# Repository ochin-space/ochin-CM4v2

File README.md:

# ochin_CM4 v2.0.1
The öchìn CM4 it’s a tiny carrier board for the Raspberry Pi Compute Module  It is designed for applications where a powerful machine with low consumption and small dimensions is required. The small form factor makes it interesting for all those applications where the space available is not much and containing the weight is important, such as in robotics, home automation and IOT.

The board is compatible with all Raspberry Pi CM4 modules equipped with eMMC. Depending on your needs, you can select a CM4 module with an SDRAM starting from 1GB up to 8GB and the eMMC from 8GB up to 32GB, with or without the Wi-Fi/BT module.

Key features of the Raspberry Pi CM4 available on öchìn are as follows:
* Broadcom BCM2711, Quad core Cortex-A72 (ARM v8) 64-bit SoC @ 1.5GHz
* Small Footprint 55mm × 40mm × 4.7mm module
* H.265 (HEVC) (up to 4Kp60 decode), H.264 (up to 1080p60 decode, 1080p30 encode)
* OpenGL ES 3.0 graphics
* Options for 1GB, 2GB, 4GB or 8GB LPDDR4-3200 SDRAM with ECC
* Options for 8GB, 16GB, or 32GB eMMC Flash
o Peak eMMC bandwidth 100MBytes/s
o 2.4 GHz, 5.0 GHz IEEE 802.11 b/g/n/ac wireless
o Bluetooth 5.0, BLE
o On board electronic switch to select between PCB trace or external antenna
* 1×USB 2.0 port (highspeed)

The öchìn CM4v2 board provides the following interfaces:

*	4x USB 2.0 480Mbps (4x SM04B-GHS-TB(LF)(SN) connectors)
*	1x USB Type-C (for flashing eMMC)
*	2x CSI camera (2x FH12-22S-0.5SH (55) connectors)
*	I2C1 (SM04B-GHS-TB(LF)(SN) connector)
*	SPI1 / 6 (SM06B-GHS-TB(LF)(SN) connector)
*	UART0 / 1 + Video Out (SM06B-GHS-TB(LF)(SN) connector)
*	UART4 / UART5 (SM06B-GHS-TB(LF)(SN) connector)
*	1x Ethernet transformerless 100Base-T
*	1x microHDMI
*	2x general purpose LEDs
*	1x RGB LED on external tiny board
*	1x general purpose button on external tiny board

The ochin_CM4v2 card introduces several new features compared to v1, some of which expand the board's capabilities and make it suitable for a wider range of embedded applications. 

Below is a table in which it is possible to see which are the new fetures and which has been removed.

In this repository you can find the [manual](öchìnCM4v2-Manual.pdf) of the board, a quick start guide for flashing the CM4 module and a guide with some tips on how to make the connections to the ochin board. 

It is important to read them both before turning on the ochin_CM4v2 board, to know its characteristics and above all the sequence in which the signals are present on the connectors.

# Intended Use

The öchìn CM4v2 is a general-purpose carrier board intended for civilian applications such as embedded computing, robotics, IoT, home automation, multimedia, computer vision, research and education.

The board is not designed, marketed or intended for military or weapons-related applications. Users are responsible for ensuring that their use of the hardware and software complies with all applicable laws, regulations and export-control requirements.

# Where to buy the ochin_CM4 boards
The ochin_CM4 boards are manufactured and sold by Seeedstudio. You can purchase ochin_CM4 boards from Seeedstudio's marketplace, https://www.seeedstudio.com or from Seeedstudio's business partners (Digikey, Mouser, RS components and many others).

# License Notice for This GitHub Repository

This GitHub repository contains various resources that are subject to specific licenses. Please note the following information regarding the applicable licenses:

* Documentation, Manuals, PDF Schematics, scripts and Other Textual Content: All textual documents present in this repository, including manuals, schematics, and documentation, are released under the GNU Free Documentation License (GFDL).

* Hardware (KiCad Sources, Gerber Files, Assembly Files, etc.): The hardware-related items, including but not limited to KiCad sources, Gerber files, and assembly files, are subject to a proprietary license. This means that these resources are not released as open source and their use is governed by the terms specified in the accompanying documentation or separate terms of use provided.

Please respect the conditions of both licenses when using and distributing the materials in this repository.

For any questions or clarifications regarding the [LICENSE](LICENSE), feel free to contact us.

# Important!!!

Print and use the extractor for the CM4 module if you don't want to break the mezzanines, you can find the [ochin_mount-extractor.stl](3d/CoversTurretsAndExtractors/ochin_mount-extractor.stl) in the "3d/CoversTurretsAndExtractors" section of this repository.

Take a look at the [öchìnCM4v2-WiringAndSuggestions.pdf](öchìnCM4v2-WiringAndSuggestions.pdf) before power the board on, it may save your time and your devices.

Never trust the color code of the GHS cables, the sequence in which commercial GHS cables are assembled is often random and does not reflect the sequence of the signals present in the connectors of the ochin_CM4 board.

Please refer to the file [öchìnCM4v2-HW-bugs.pdf](öchìnCM4v2-HW-bugs.pdf) for details regarding known issues on the board and the respective version in which they were resolved

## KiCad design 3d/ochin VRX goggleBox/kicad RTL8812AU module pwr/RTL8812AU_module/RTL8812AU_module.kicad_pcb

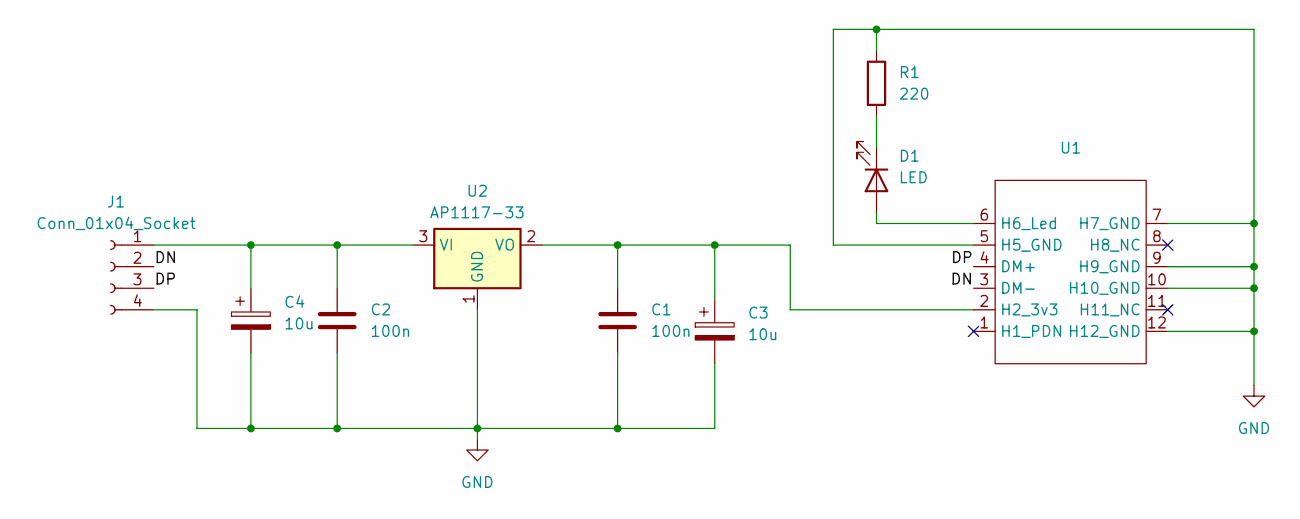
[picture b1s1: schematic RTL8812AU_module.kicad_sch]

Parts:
C1, C2: 100n; C_0805_2012Metric_Pad1.18x1.45mm_HandSolder
C3, C4: 10u; CP_EIA-3216-10_Kemet-I_Pad1.58x1.35mm_HandSolder
D1: LED; LED_0805_2012Metric_Pad1.15x1.40mm_HandSolder
J1: Conn_01x04_Socket; PinHeader_1x04_P2.54mm_Vertical
R1: 220; R_0805_2012Metric_Pad1.20x1.40mm_HandSolder
U1: RTL8812AU
U2: AP1117-33; SOT-223-3_TabPin2

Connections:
/DN: J1.2, U1.3 (DM-)
/DP: J1.3, U1.4 (DM+)
GND: C1.2, C2.2, C3.2, C4.2, J1.4, R1.1, U1.5 (H5_GND), U1.7 (H7_GND), U1.9 (H9_GND), U1.10 (H10_GND), U1.12 (H12_GND), U2.1 (GND)
unnamed: D1.2 (A), U1.6 (H6_Led)
unnamed: D1.1 (K), R1.2
unnamed: C2.1, C4.1, J1.1, U2.3 (VI)
unnamed: C1.1, C3.1, U1.2 (H2_3v3), U2.2 (VO)

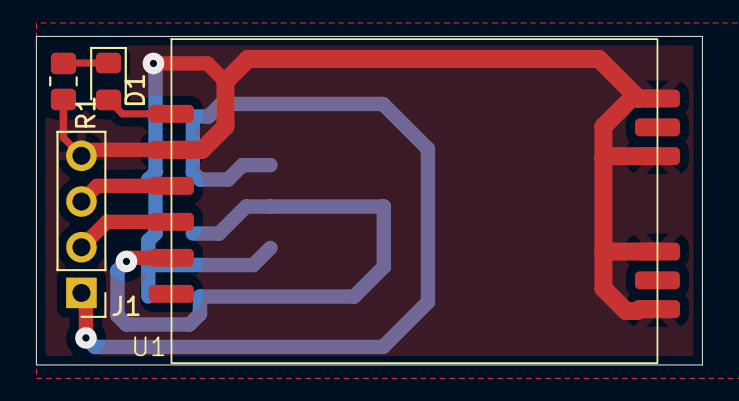
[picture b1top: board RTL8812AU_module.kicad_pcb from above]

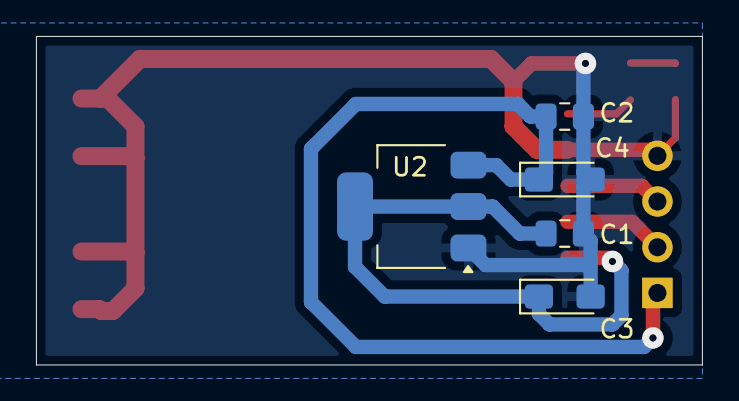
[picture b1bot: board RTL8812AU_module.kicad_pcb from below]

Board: 2 copper layers, 37.0 x 18.2 mm, 9 parts (5 on the bottom side), 7 nets.

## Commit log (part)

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2023-08-27 first commit for the ochin_CM4v2
2023-09-18 updated sch
2023-09-18 added sch
2023-09-19 sch updated
2023-09-19 updated manual
2023-10-30 updated docs
2023-10-30 updated readme image
2024-02-12 updated docs for v2
2024-02-12 updated 3d files
2024-02-12 added python scripts
2024-02-29 added hw tests
2024-07-31 license update to GFDL
2024-08-09 fixed USB ext pinout description in image and manuals
2024-11-25 added HW buglist file updated README.md
2024-11-25 updated buglist
2025-01-09 -updated the schematic of V2.0.1 -updated HW bugs list
2025-05-02 updated docs for v2.0.1
2025-05-12 added VRX goggleBox
2025-05-13 index.md added for git pages
